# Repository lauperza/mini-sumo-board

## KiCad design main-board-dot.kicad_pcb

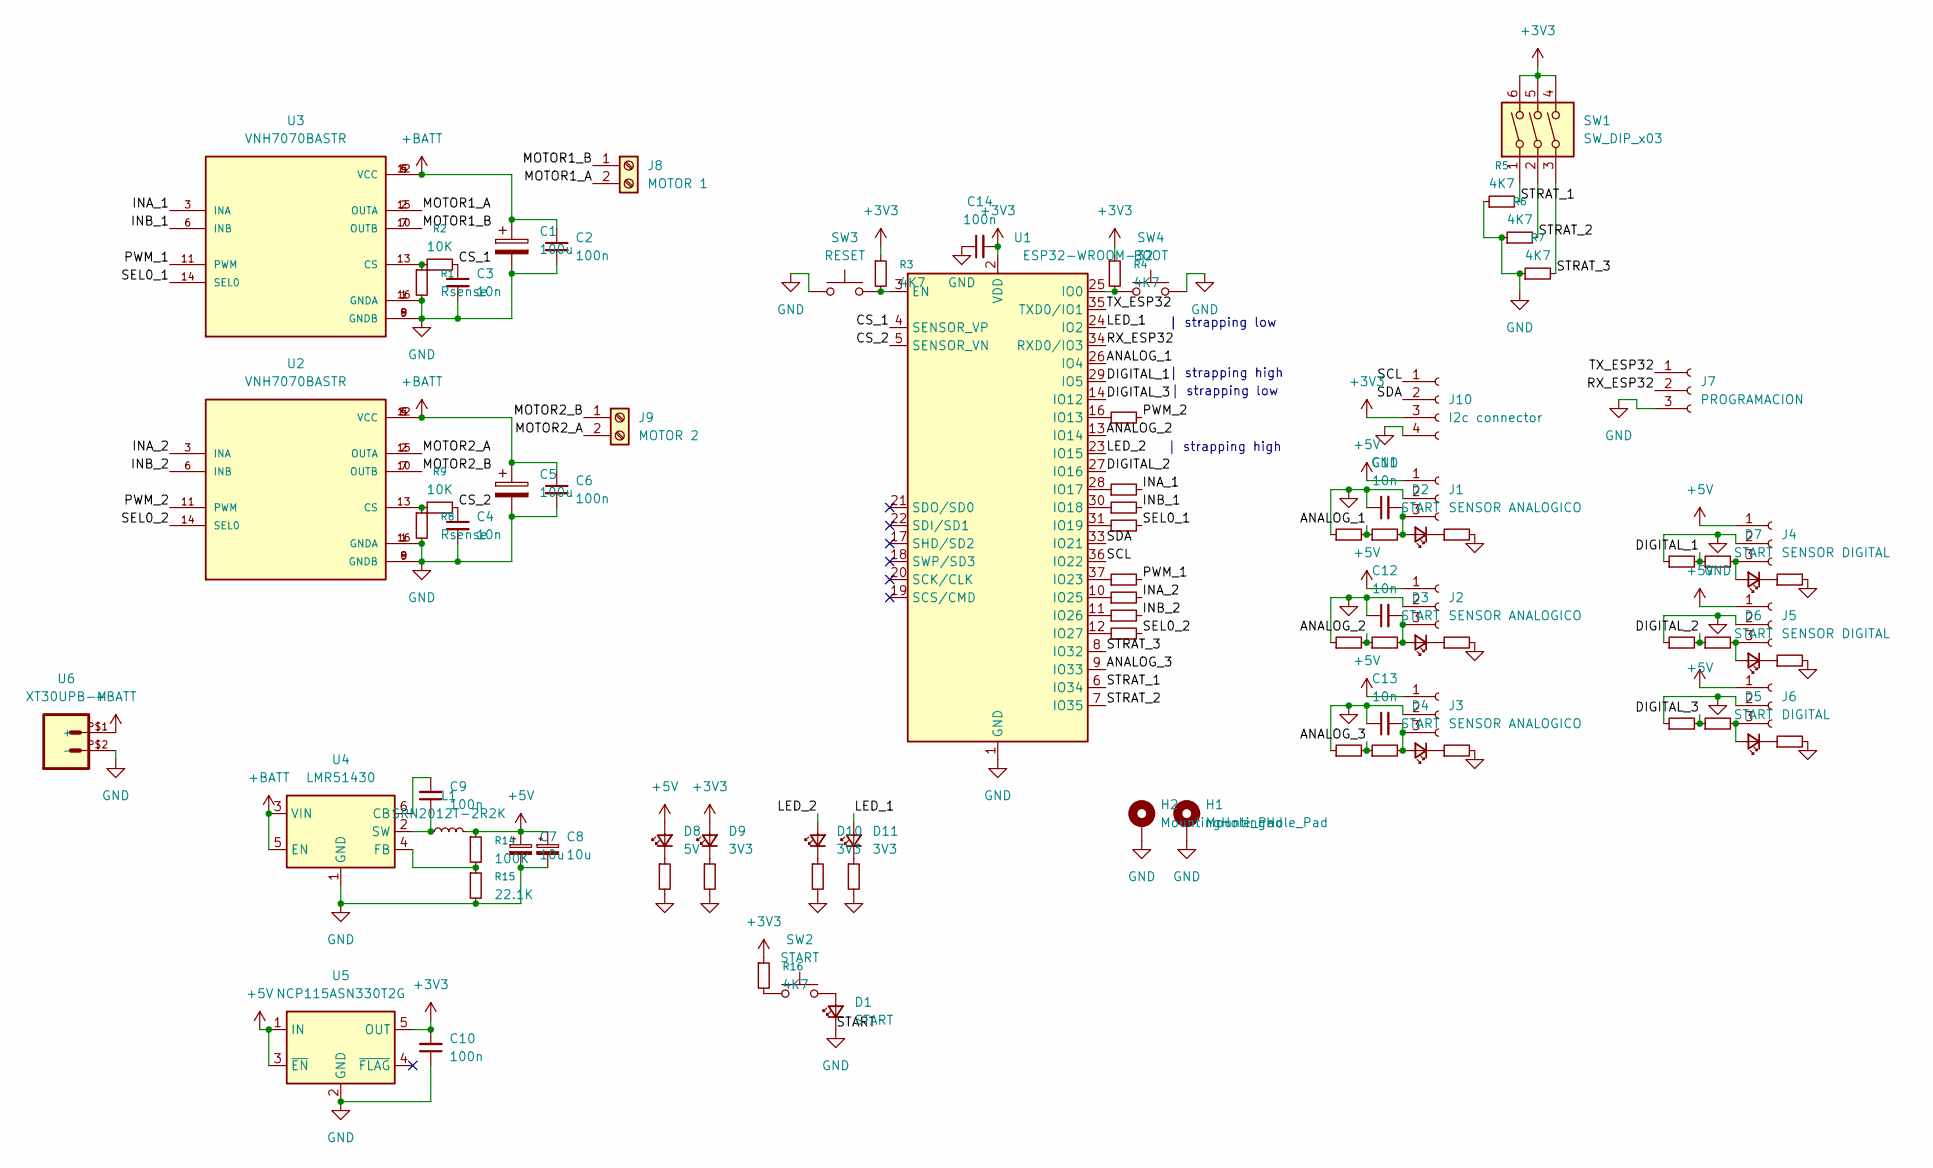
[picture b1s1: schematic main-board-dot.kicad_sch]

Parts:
C1, C5: 100u; CP_EIA-6032-28_Kemet-C_HandSolder
C2, C6, C9, C10, C14: 100n; C_0805_2012Metric_Pad1.18x1.45mm_HandSolder
C3, C4, C11, C12, C13: 10n; C_0805_2012Metric_Pad1.18x1.45mm_HandSolder
C7, C8: 10u; CP_EIA-3216-18_Kemet-A_HandSolder
D1, D2, D3, D4, D5, D6, D7: START; LED_0805_2012Metric_Pad1.15x1.40mm_HandSolder
D8: 5V; LED_0805_2012Metric_Pad1.15x1.40mm_HandSolder
D9, D10, D11: 3V3; LED_0805_2012Metric_Pad1.15x1.40mm_HandSolder
H1, H2: MountingHole_Pad; MountingHole_2.2mm_M2_Pad
J1, J2, J3: SENSOR ANALOGICO; PinSocket_1x03_P2.54mm_Horizontal
J4, J5: SENSOR DIGITAL; PinSocket_1x03_P2.54mm_Horizontal
J6: DIGITAL; PinSocket_1x03_P2.54mm_Horizontal
J7: PROGRAMACION; PinSocket_1x03_P2.54mm_Horizontal
J8: MOTOR 1; BORNERA2_AZUL
J9: MOTOR 2; BORNERA2_AZUL
J10: I2c connector; PinSocket_1x04_P2.54mm_Vertical
L1: SRN2012T-2R2K; L_0805_2012Metric_Pad1.05x1.20mm_HandSolder
R1, R8: Rsense; R_0805_2012Metric_Pad1.20x1.40mm_HandSolder
R2, R9: 10K; R_0805_2012Metric_Pad1.20x1.40mm_HandSolder
R3, R4, R5, R6, R7, R16: 4K7; R_0805_2012Metric_Pad1.20x1.40mm_HandSolder
R10, R11, R12, R13, R17, R18, R19, R20, R21, R22, R23, R24, R25, R26, R27, R28, R29, R30, R31, R32, R33, R34, R35, R36, R37, R38, R39, R40, R41, R42: 330; R_0805_2012Metric_Pad1.20x1.40mm_HandSolder
R14: 100K; R_0805_2012Metric_Pad1.20x1.40mm_HandSolder
R15: 22.1K; R_0805_2012Metric_Pad1.20x1.40mm_HandSolder
SW1: SW_DIP_x03; SW_DIP_SPSTx03_Slide_6.7x9.18mm_W8.61mm_P2.54mm_LowProfile
SW2: START; SW_PUSH_6mm
SW3: RESET; SW_Push_SPST_NO_Alps_SKRK
SW4: BOOT; SW_Push_SPST_NO_Alps_SKRK
U1: ESP32-WROOM-32
U2, U3: VNH7070BASTR; SOIC127P600X175-16N; PARTREV 2
U4: LMR51430; SOT-23-6
U5: NCP115ASN330T2G; TSOP-5_1.65x3.05mm_P0.95mm
U6: XT30UPB-M

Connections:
+3V3: C10.2, C14.2, D9.2 (A), J10.3, R3.1, R4.1, R16.1, SW1.4, SW1.5, SW1.6, U1.2 (VDD), U5.5 (OUT)
+5V: C7.1, C8.1, D8.2 (A), J1.1, J2.1, J3.1, J4.1, J5.1, J6.1, L1.2, R14.1, U5.1 (IN), U5.3 (~EN)
+BATT: C1.1, C2.1, C5.1, C6.1, U2.4 (VCC), U2.5 (VCC), U2.12 (VCC), U3.4 (VCC), U3.5 (VCC), U3.12 (VCC), U4.3 (VIN), U4.5 (EN), U6.P$1 (+)
/ANALOG_1: R17.1, R23.2, U1.26 (IO4)
/ANALOG_2: R18.1, R24.2, U1.13 (IO14)
/ANALOG_3: R19.1, R25.2, U1.9 (IO33)
/CS_1: C3.1, R2.2, U1.4 (SENSOR_VP)
/CS_2: C4.1, R9.2, U1.5 (SENSOR_VN)
/DIGITAL_1: R20.2, R21.1, U1.29 (IO5)
/DIGITAL_2: R22.2, R26.1, U1.27 (IO16)
/DIGITAL_3: R27.2, R28.1, U1.14 (IO12)
/INA_1: R11.2, U3.3 (INA)
/INA_2: R29.2, U2.3 (INA)
/INB_1: R12.2, U3.6 (INB)
/INB_2: R30.2, U2.6 (INB)
/LED_1: D11.2 (A), U1.24 (IO2)
/LED_2: D10.2 (A), U1.23 (IO15)
/MOTOR1_A: J8.2, U3.2 (OUTA), U3.15 (OUTA)
/MOTOR1_B: J8.1, U3.7 (OUTB), U3.10 (OUTB)
/MOTOR2_A: J9.2, U2.2 (OUTA), U2.15 (OUTA)
/MOTOR2_B: J9.1, U2.7 (OUTB), U2.10 (OUTB)
/PWM_1: R10.2, U3.11 (PWM)
/PWM_2: R32.2, U2.11 (PWM)
/RX_ESP32: J7.2, U1.34 (RXD0/IO3)
/SCL: J10.1, U1.36 (IO22)
/SDA: J10.2, U1.33 (IO21)
/SEL0_1: R13.2, U3.14 (SEL0)
/SEL0_2: R31.2, U2.14 (SEL0)
/STRAT_1: R5.2, SW1.1, U1.6 (IO34)
/STRAT_2: R6.2, SW1.2, U1.7 (IO35)
/STRAT_3: R7.2, SW1.3, U1.8 (IO32)
/TX_ESP32: J7.1, U1.35 (TXD0/IO1)
GND: C1.2, C2.2, C3.2, C4.2, C5.2, C6.2, C7.2, C8.2, C10.1, C11.1, C12.1, C13.1, C14.1, D1.1 (K), H1.1, H2.1, J1.2, J2.2, J3.2, J4.2, J5.2, J6.2, J7.3, J10.4, R1.2, R5.1, R6.1, R7.1, R8.2, R15.2, R20.1, R22.1, R23.1, R24.1, R25.1, R27.1, R33.2, R34.2, R35.2, R36.2, R37.2, R38.2, R39.2, R40.2, R41.2, R42.2, SW3.1, SW4.2, U1.1 (GND), U1.15 (GND), U1.38 (GND), U1.39 (GND), U2.1 (GNDA), U2.8 (GNDB), U2.9 (GNDB), U2.16 (GNDA), U3.1 (GNDA), U3.8 (GNDB), U3.9 (GNDB), U3.16 (GNDA), U4.1 (GND), U5.2 (GND), U6.P$2 (-)
unnamed: D1.2 (A), SW2.2
unnamed: C11.2, D2.2 (A), J1.3, R17.2
unnamed: D2.1 (K), R33.1
unnamed: C12.2, D3.2 (A), J2.3, R18.2
unnamed: D3.1 (K), R34.1
unnamed: C13.2, D4.2 (A), J3.3, R19.2
unnamed: D4.1 (K), R35.1
unnamed: D5.2 (A), J6.3, R28.2
unnamed: D5.1 (K), R36.1
unnamed: D6.2 (A), J5.3, R26.2
unnamed: D6.1 (K), R37.1
unnamed: D7.2 (A), J4.3, R21.2
unnamed: D7.1 (K), R38.1
unnamed: D8.1 (K), R39.1
unnamed: D9.1 (K), R40.1
unnamed: D10.1 (K), R41.1
unnamed: D11.1 (K), R42.1
unnamed: R16.2, SW2.1
unnamed: R3.2, SW3.2, U1.3 (EN)
unnamed: R4.2, SW4.1, U1.25 (IO0)
unnamed: R32.1, U1.16 (IO13)
unnamed: R11.1, U1.28 (IO17)
unnamed: R12.1, U1.30 (IO18)
unnamed: R13.1, U1.31 (IO19)
unnamed: R10.1, U1.37 (IO23)
unnamed: R29.1, U1.10 (IO25)
unnamed: R30.1, U1.11 (IO26)
unnamed: R31.1, U1.12 (IO27)
unnamed: R8.1, R9.1, U2.13 (CS)
unnamed: R1.1, R2.1, U3.13 (CS)
unnamed: C9.2, U4.6 (CB)
unnamed: R14.2, R15.1, U4.4 (FB)
unnamed: C9.1, L1.1, U4.2 (SW)

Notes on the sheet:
| strapping high
| strapping low

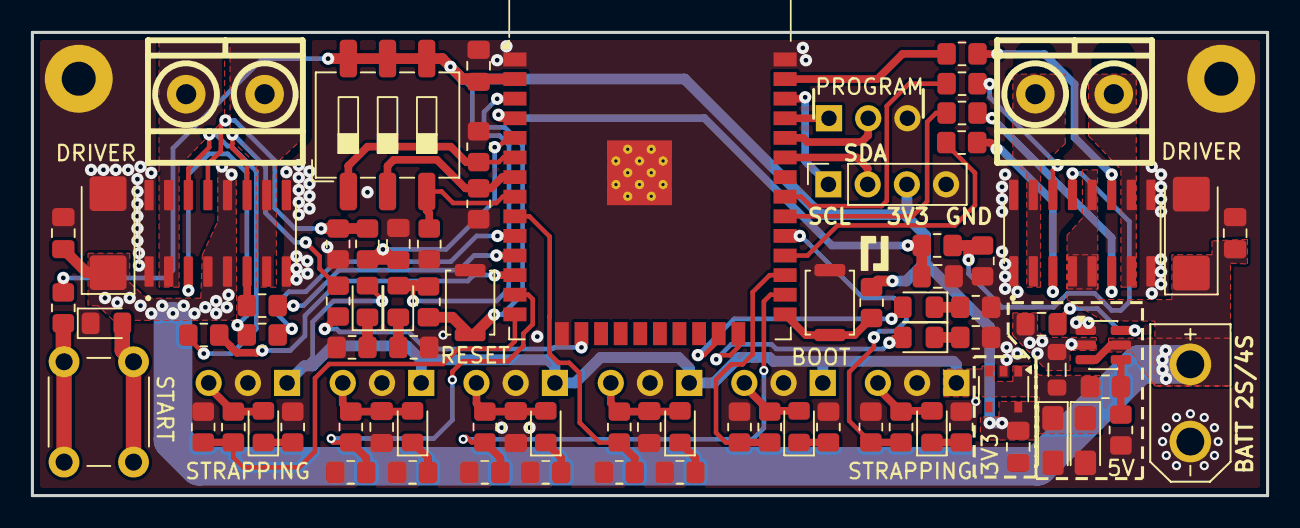
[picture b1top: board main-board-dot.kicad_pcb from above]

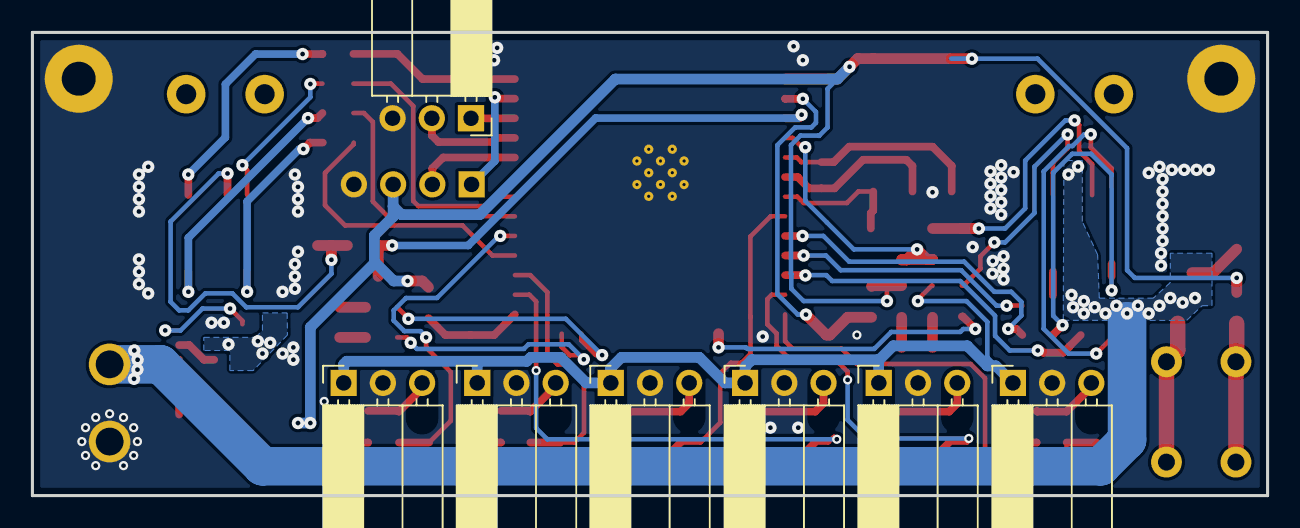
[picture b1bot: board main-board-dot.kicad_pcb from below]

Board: 2 copper layers, 80.0 x 30.0 mm, 90 parts (7 on the bottom side), 66 nets.

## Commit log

2025-10-14 proyecto
2025-10-14 esquematico
2025-10-16 LICENSE
